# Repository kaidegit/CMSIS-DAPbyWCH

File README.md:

Maybe it is the cheapest cmsis-dap debugger. 

[Official description](http://www.wch.cn/products/WCH-Link.html?from=search&wd=eyJpdiI6IjMyRDc0Z2dCV2g2UkVINldPaUtHWXc9PSIsInZhbHVlIjoiWndXN2d5OFhMUkt2UGZQZnF1Z1lcL0E9PSIsIm1hYyI6ImNkMDcwNzQ0YmNjOGZkNjkxN2IwZGFlNjY3ZDhmYTA3MmZjNDZmNTg0OTQ4MjM4ZWIwZTYzODAyY2Y5NDMxOWIifQ==)

[Official schematic and mannual](http://www.wch.cn/bbs/thread-71088-1.html)
# Hardward
The main MCU is CH549F, which has a lot of advantages.
* cheap. The MCU is a 8051 core, and the price is less than 5RMB. It is cheaper than CH32F103 to make a CMSIS-DAP debugger.
* easy to soldering. The MCU is an SOP-16 package. 
* can also be small. The CH549 also have a QFN28 package. 
* can debug both ARM and RISC-V core MCU. (The target MCU should support SWD)

# Firmware
The firmware is extract from MounRiver Studio.

# Screenshot
MDK-ARM

openocd

size

# How to Flash
* short connect the 1.27mm pin hole
* plug in the type-c connector
* open the WCHISPTool.(The installer is in "tools" folder)
* choose the 8-bit CH54X series, set the MCU model to CH549, set the download way to USB, select the erase the DataFlash, choose the right USB device and the user program file(use WCHLINK_V1.2.bin)
* click the flash button.
* if all goes well, you will see the success count adding one. You can plug off and plug in the DIY WCH-Link. If the 2 LEDs are all on, plug off it and short connect the TX and GND and plug in.

# How to Use
* When using MDK-ARM, it can be use as a normal CMSIS-DAP debugger. However, when using openocd to drive the WCH-Link, you should define the vid and pid by using the code 
  
  `cmsis_dap_vid_pid 0x1a86 0x8011`
  
  In command line, the code should be before "-c" parameter. while in .cfg file, it should be added as above picture.

for more information, check the documents in "documents" folder.

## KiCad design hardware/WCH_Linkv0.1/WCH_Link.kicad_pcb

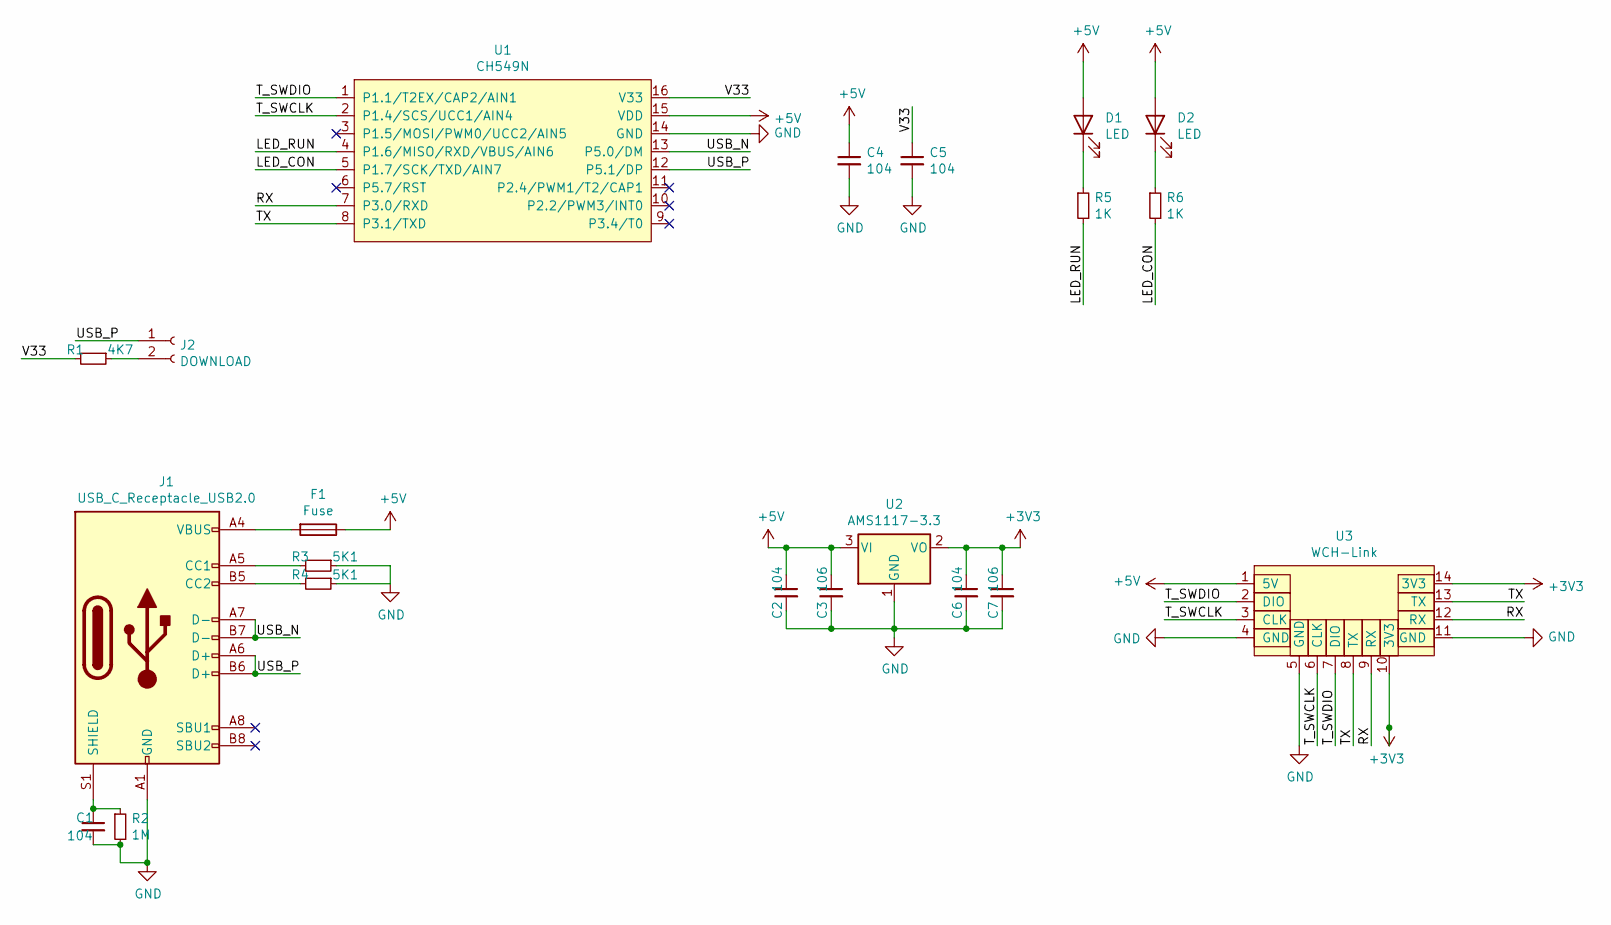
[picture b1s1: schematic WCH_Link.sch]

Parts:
C1, C2, C4, C5, C6: 104; C_0603_1608Metric_Pad1.05x0.95mm_HandSolder
C3, C7: 106; C_0603_1608Metric_Pad1.05x0.95mm_HandSolder
D1, D2: LED; D_0603_1608Metric_Pad1.05x0.95mm_HandSolder
F1: Fuse; Fuse_0805_2012Metric_Pad1.15x1.40mm_HandSolder
J1: USB_C_Receptacle_USB2.0; USB_C_Receptacle_HRO_TYPE-C-31-M-12
J2: DOWNLOAD; PinHeader_1x02_P1.27mm_Horizontal
R1: 4K7; R_0603_1608Metric_Pad0.98x0.95mm_HandSolder
R2: 1M; R_0603_1608Metric_Pad0.98x0.95mm_HandSolder
R3, R4: 5K1; R_0603_1608Metric_Pad0.98x0.95mm_HandSolder
R5, R6: 1K; R_0603_1608Metric_Pad0.98x0.95mm_HandSolder
U1: CH549N; SOP-16_3.9x9.9mm_P1.27mm
U2: AMS1117-3.3; SOT-223-3_TabPin2
U3: WCH-Link

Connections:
+3V3: C6.1, C7.1, U2.2 (VO), U3.10 (3V3), U3.14 (3V3)
+5V: C2.1, C3.1, C4.1, D1.2 (A), D2.2 (A), F1.1, U1.15 (VDD), U2.3 (VI), U3.1 (5V)
/LED_CON: R6.2, U1.5 (P1.7/SCK/TXD/AIN7)
/LED_RUN: R5.2, U1.4 (P1.6/MISO/RXD/VBUS/AIN6)
/RX: U1.7 (P3.0/RXD), U3.9 (RX), U3.12 (RX)
/TX: U1.8 (P3.1/TXD), U3.8 (TX), U3.13 (TX)
/T_SWCLK: U1.2 (P1.4/SCS/UCC1/AIN4), U3.3 (CLK), U3.6 (CLK)
/T_SWDIO: U1.1 (P1.1/T2EX/CAP2/AIN1), U3.2 (DIO), U3.7 (DIO)
/USB_N: J1.A7 (D-), J1.B7 (D-), U1.13 (P5.0/DM)
/USB_P: J1.A6 (D+), J1.B6 (D+), J2.1, U1.12 (P5.1/DP)
/V33: C5.1, R1.2, U1.16 (V33)
GND: C1.2, C2.2, C3.2, C4.2, C5.2, C6.2, C7.2, J1.A1 (GND), J1.A12 (GND), J1.B1 (GND), J1.B12 (GND), R2.2, R3.1, R4.1, U1.14 (GND), U2.1 (GND), U3.4 (GND), U3.5 (GND), U3.11 (GND)
unnamed: C1.1, J1.S1 (SHIELD), R2.1
unnamed: D1.1 (K), R5.1
unnamed: D2.1 (K), R6.1
unnamed: F1.2, J1.A4 (VBUS), J1.A9 (VBUS), J1.B4 (VBUS), J1.B9 (VBUS)
unnamed: J1.A5 (CC1), R3.2
unnamed: J1.B5 (CC2), R4.2
unnamed: J2.2, R1.1

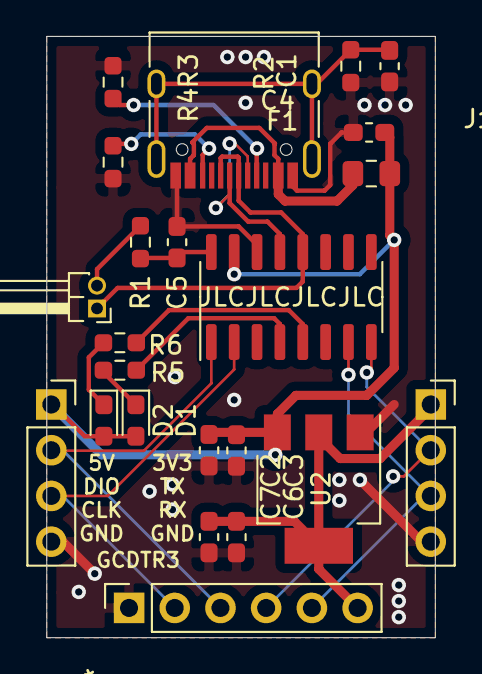
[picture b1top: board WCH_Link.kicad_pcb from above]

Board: 2 copper layers, 21.6 x 33.4 mm, 20 parts (0 on the bottom side), 15 nets.

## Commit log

2021-02-07 first upload
